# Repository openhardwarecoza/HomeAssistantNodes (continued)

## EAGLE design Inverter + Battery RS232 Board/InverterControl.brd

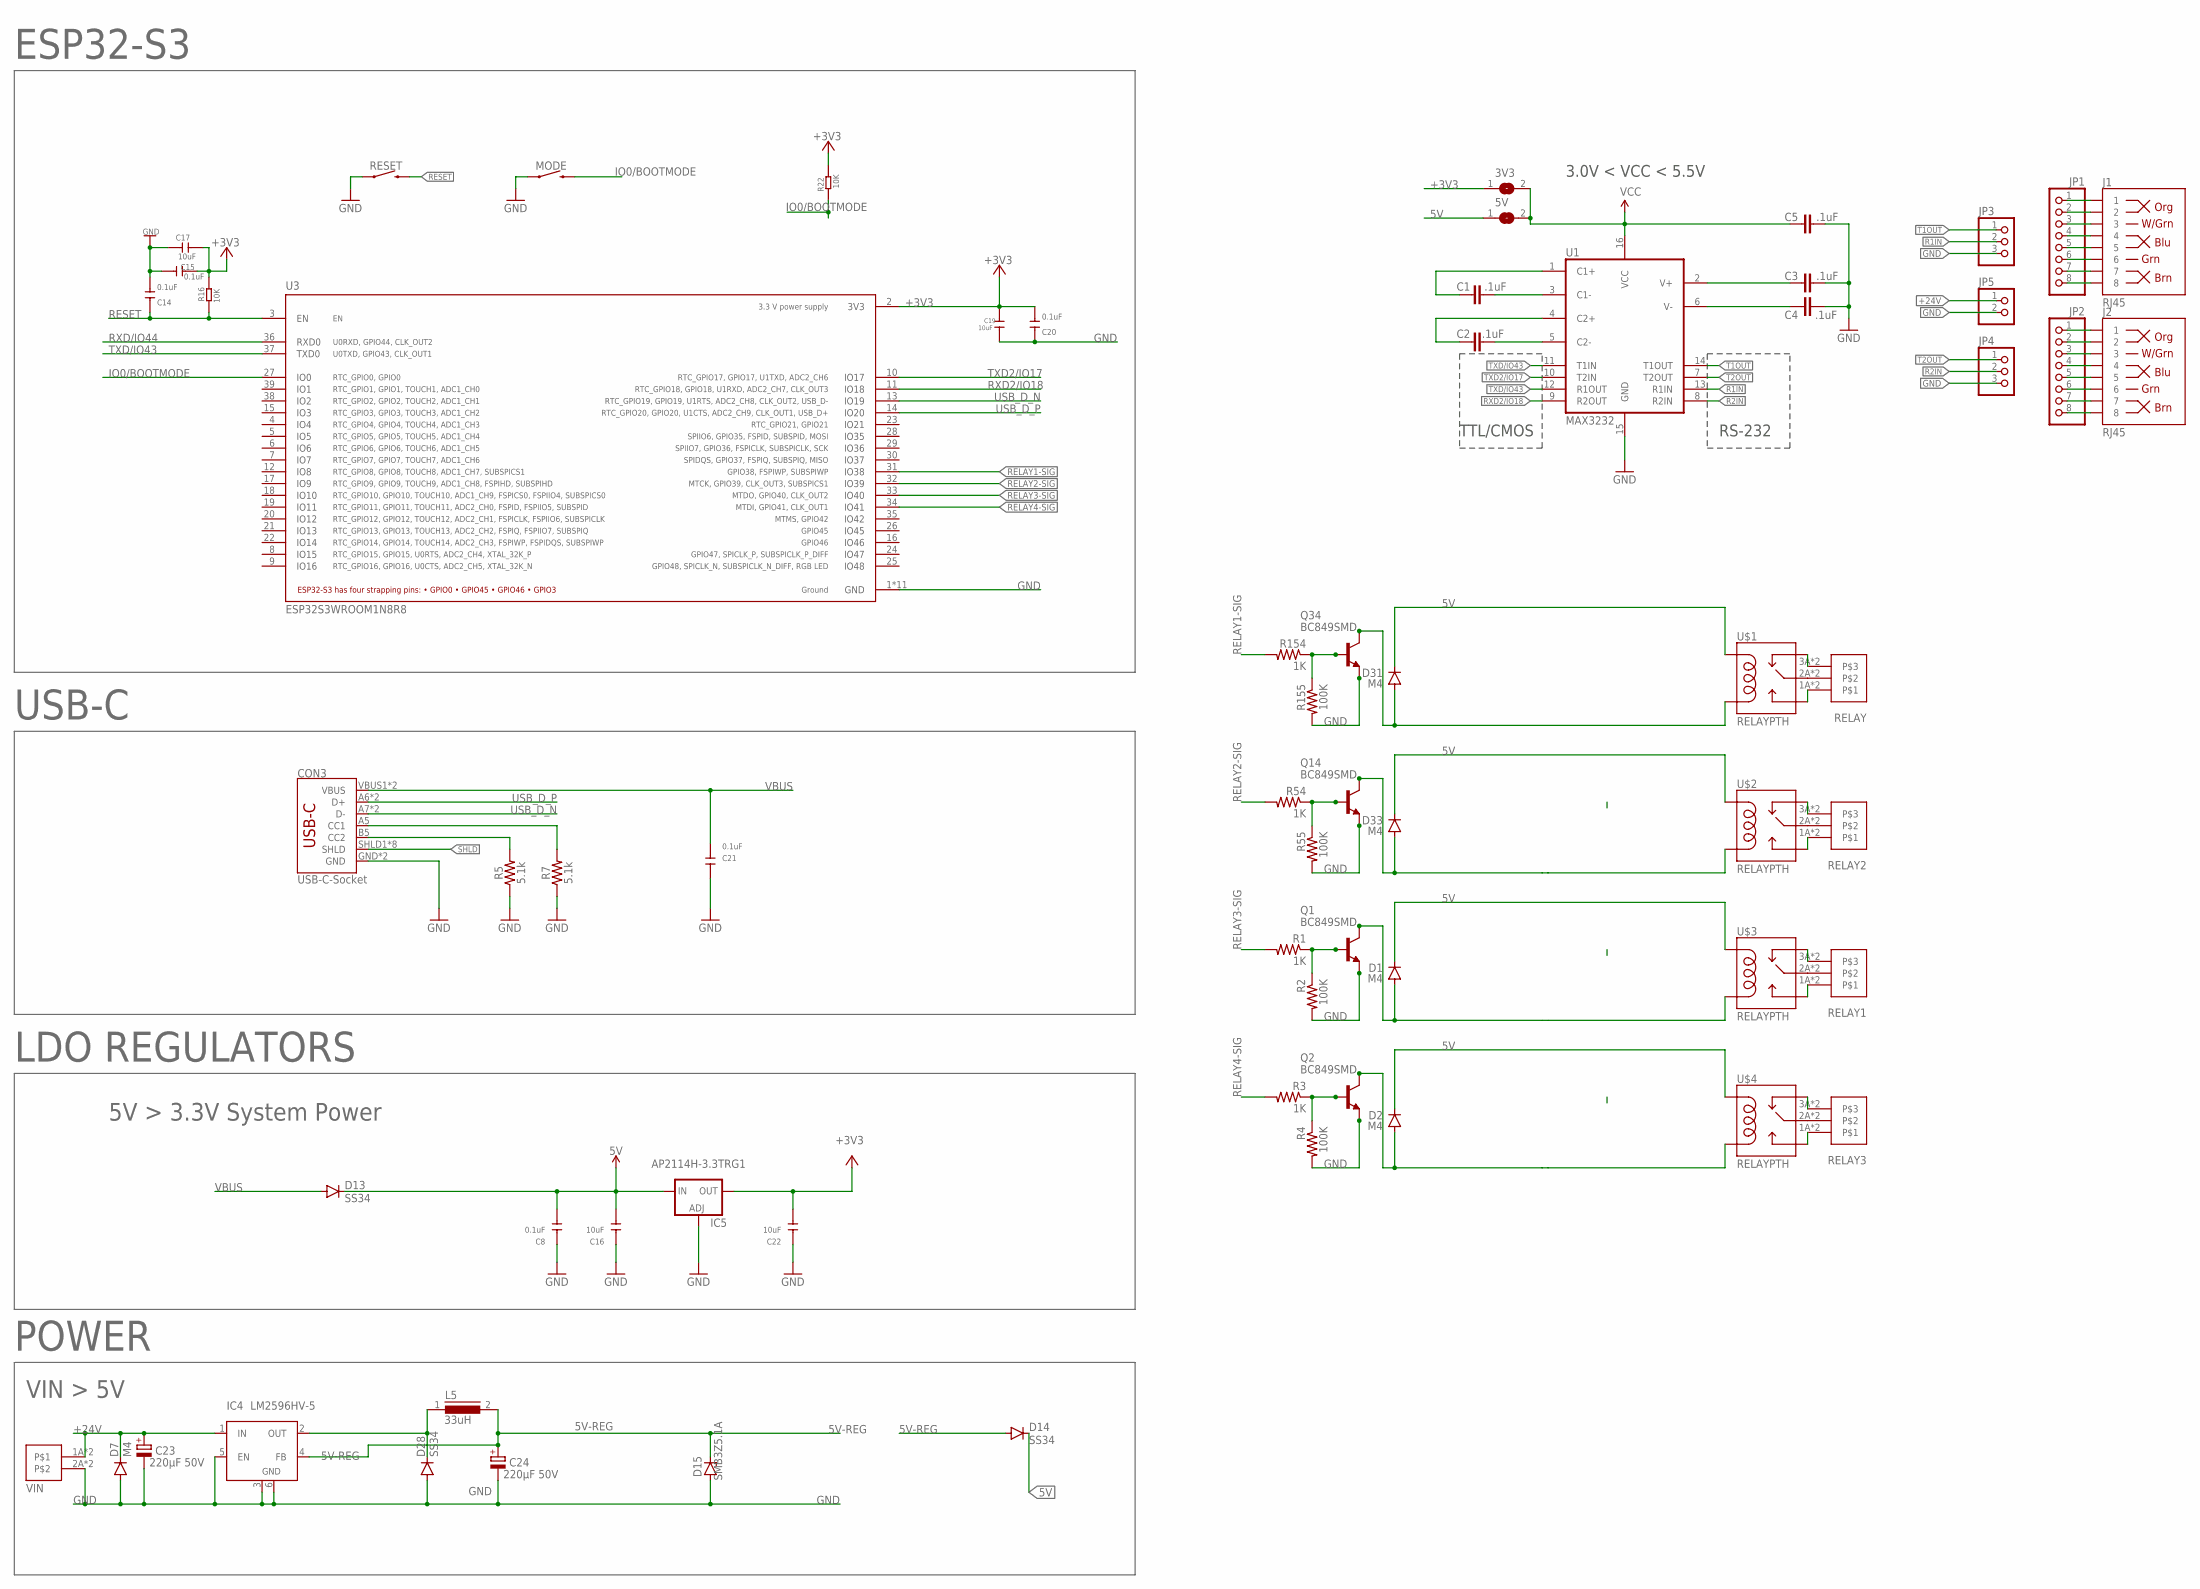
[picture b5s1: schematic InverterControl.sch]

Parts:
3V3, 5V: SJ
C1, C2, C3, C4, C5: .1uF; 0603-CAP
C8, C14, C15, C20, C21: 0.1uF; DISCRETE_C1206
C16, C19, C22: 10uF; C1206
C17: 10uF; DISCRETE_C1206
C23, C24: 220µF 50V; PANASONIC_E
CON3: USB-C-Socket; USB-C-16P
D1, D2, D7, D31, D33: M4; DO-214AC
D13: SS34; DO-214AC
D14, D28: SS34; SMB
D15: SMB3Z5.1A; SMB
IC4: LM2596HV-5; TO263-5
IC5: AP2114H-3.3TRG1; SOT223
J1, J2: RJ45; RJ45-8
JP1, JP2: PINHD-1X8; 1X08
JP3, JP4: PINHD-1X3; 1X03
JP5: PINHD-1X2; 1X02
L5: 33uH; DR127
MODE: MOMENTARY-SWITCH-SPST-PTH-6.0MM; TACTILE_SWITCH_PTH_6.0MM
Q1, Q2, Q14, Q34: BC849SMD; SOT23-BEC
R1, R3, R54, R154: 1K; R1206
R2, R4, R55, R155: 100K; R1206
R5, R7: 5.1k; 0603@1
R16, R22: 10K; R1206
RELAY, RELAY1, RELAY2, RELAY3: WJ212R-THR-3.5-3
RESET: MOMENTARY-SWITCH-SPST-PTH-6.0MM; TACTILE_SWITCH_PTH_6.0MM
U1: MAX3232; SO016
U3: ESP32S3WROOM1N8R8; XCVR_ESP32S3WROOM1N8R8
U$1, U$2, U$3, U$4: RELAYPTH; SRD-05VDC-SL-C
VIN: WJ212R-THR-3.5-2

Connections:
5V: 5V.1, C8.2, C16.1, D1.C, D2.C, D13.C, D14.C, D31.C, D33.C, IC5.3 (IN), U$1.COIL1, U$2.COIL1, U$3.COIL1, U$4.COIL1
5V-REG: C24.+, D14.A, D15.C, IC4.4 (FB), L5.2
+3V3: 3V3.1, C15.1, C17.1, C19.1, C20.2, C22.1, IC5.4 (OUT), R16.2, R22.2, U3.2 (3V3)
+24V: C23.+, D7.C, IC4.1 (IN), JP5.1, VIN.1A, VIN.1B
C1+: C1.1, U1.1 (C1+)
C1-: C1.2, U1.3 (C1-)
C2+: C2.1, U1.4 (C2+)
C2-: C2.2, U1.5 (C2-)
CC1: CON3.A5 (CC1), R7.2
CC2: CON3.B5 (CC2), R5.2
COIL-1: D31.A, Q34.C, U$1.COIL0
COIL-2: D33.A, Q14.C, U$2.COIL0
COIL-3: D1.A, Q1.C, U$3.COIL0
COIL-4: D2.A, Q2.C, U$4.COIL0
GND: C3.2, C4.2, C5.2, C8.1, C14.2, C15.2, C16.2, C17.2, C19.2, C20.1, C21.1, C22.2, C23.-, C24.-, CON3.GND, CON3.GND2 (GND), D7.A, D15.A, D28.A, IC4.3 (GND), IC4.5 (EN), IC4.6 (GND), IC5.1 (ADJ), JP3.3, JP4.3, JP5.2, MODE.1, Q1.E, Q2.E, Q14.E, Q34.E, R2.2, R4.2, R5.1, R7.1, R55.2, R155.2, RESET.1, U1.15 (GND), U3.1 (GND), U3.40 (GND), U3.41_1 (GND), U3.41_2 (GND), U3.41_3 (GND), U3.41_4 (GND), U3.41_5 (GND), U3.41_6 (GND), U3.41_7 (GND), U3.41_8 (GND), U3.41_9 (GND), VIN.2A, VIN.2B
IO0/BOOTMODE: MODE.3 (2), R22.1, U3.27 (IO0)
unnamed: J1.1, JP1.1
unnamed: J1.2, JP1.2
unnamed: J1.3, JP1.3
unnamed: J1.4, JP1.4
unnamed: J1.5, JP1.5
unnamed: J1.6, JP1.6
unnamed: J1.7, JP1.7
unnamed: J1.8, JP1.8
unnamed: J2.1, JP2.1
unnamed: J2.2, JP2.2
unnamed: J2.3, JP2.3
unnamed: J2.4, JP2.4
unnamed: J2.5, JP2.5
unnamed: J2.6, JP2.6
unnamed: J2.7, JP2.7
unnamed: J2.8, JP2.8
unnamed: RELAY.2A, RELAY.2B, U$1.SWCOMMON
unnamed: RELAY2.2A, RELAY2.2B, U$2.SWCOMMON
unnamed: Q1.B, R1.1, R2.1
unnamed: RELAY1.2A, RELAY1.2B, U$3.SWCOMMON
unnamed: Q2.B, R3.1, R4.1
unnamed: RELAY3.2A, RELAY3.2B, U$4.SWCOMMON
unnamed: RELAY.3A, RELAY.3B, U$1.SWCLOSED (SWCLOSE)
unnamed: RELAY.1A, RELAY.1B, U$1.SWOPEN
unnamed: RELAY2.3A, RELAY2.3B, U$2.SWCLOSED (SWCLOSE)
unnamed: RELAY2.1A, RELAY2.1B, U$2.SWOPEN
unnamed: RELAY1.3A, RELAY1.3B, U$3.SWCLOSED (SWCLOSE)
unnamed: RELAY1.1A, RELAY1.1B, U$3.SWOPEN
unnamed: Q14.B, R54.1, R55.1
unnamed: RELAY3.3A, RELAY3.3B, U$4.SWCLOSED (SWCLOSE)
unnamed: RELAY3.1A, RELAY3.1B, U$4.SWOPEN
unnamed: Q34.B, R154.1, R155.1
unnamed: D28.C, IC4.2 (OUT), L5.1
R1IN: JP3.2, U1.13 (R1IN)
R2IN: JP4.2, U1.8 (R2IN)
RELAY1-SIG: R154.2, U3.31 (IO38)
RELAY2-SIG: R54.2, U3.32 (IO39)
RELAY3-SIG: R1.2, U3.33 (IO40)
RELAY4-SIG: R3.2, U3.34 (IO41)
RESET: C14.1, R16.1, RESET.3 (2), U3.3 (EN)
RXD2/IO18: U1.9 (R2OUT), U3.11 (IO18)
RXD/IO44: U3.36 (RXD0)
SHLD: CON3.SHLD1 (SHLD), CON3.SHLD2 (SHLD), CON3.SHLD3 (SHLD), CON3.SHLD4 (SHLD), CON3.SHLD5 (SHLD), CON3.SHLD6 (SHLD), CON3.SHLD7 (SHLD), CON3.SHLD8 (SHLD)
T1OUT: JP3.1, U1.14 (T1OUT)
T2OUT: JP4.1, U1.7 (T2OUT)
TXD2/IO17: U1.10 (T2IN), U3.10 (IO17)
TXD/IO43: U1.11 (T1IN), U1.12 (R1OUT), U3.37 (TXD0)
USB_D_N: CON3.A7 (D-), CON3.B7 (D-), U3.13 (IO19)
USB_D_P: CON3.A6 (D+), CON3.B6 (D+), U3.14 (IO20)
V+: C3.1, U1.2 (V+)
V-: C4.1, U1.6 (V-)
VBUS: C21.2, CON3.VBUS1 (VBUS), CON3.VBUS2 (VBUS), D13.A
VCC: 3V3.2, 5V.2, C5.1, U1.16 (VCC)

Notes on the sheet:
ESP32-S3
5V > 3.3V System Power
USB-C
LDO REGULATORS
POWER
VIN > 5V
RS-232
TTL/CMOS
3.0V < VCC < 5.5V

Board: 4 copper layers, 67 parts (0 on the bottom side), 68 nets, no tracks yet.

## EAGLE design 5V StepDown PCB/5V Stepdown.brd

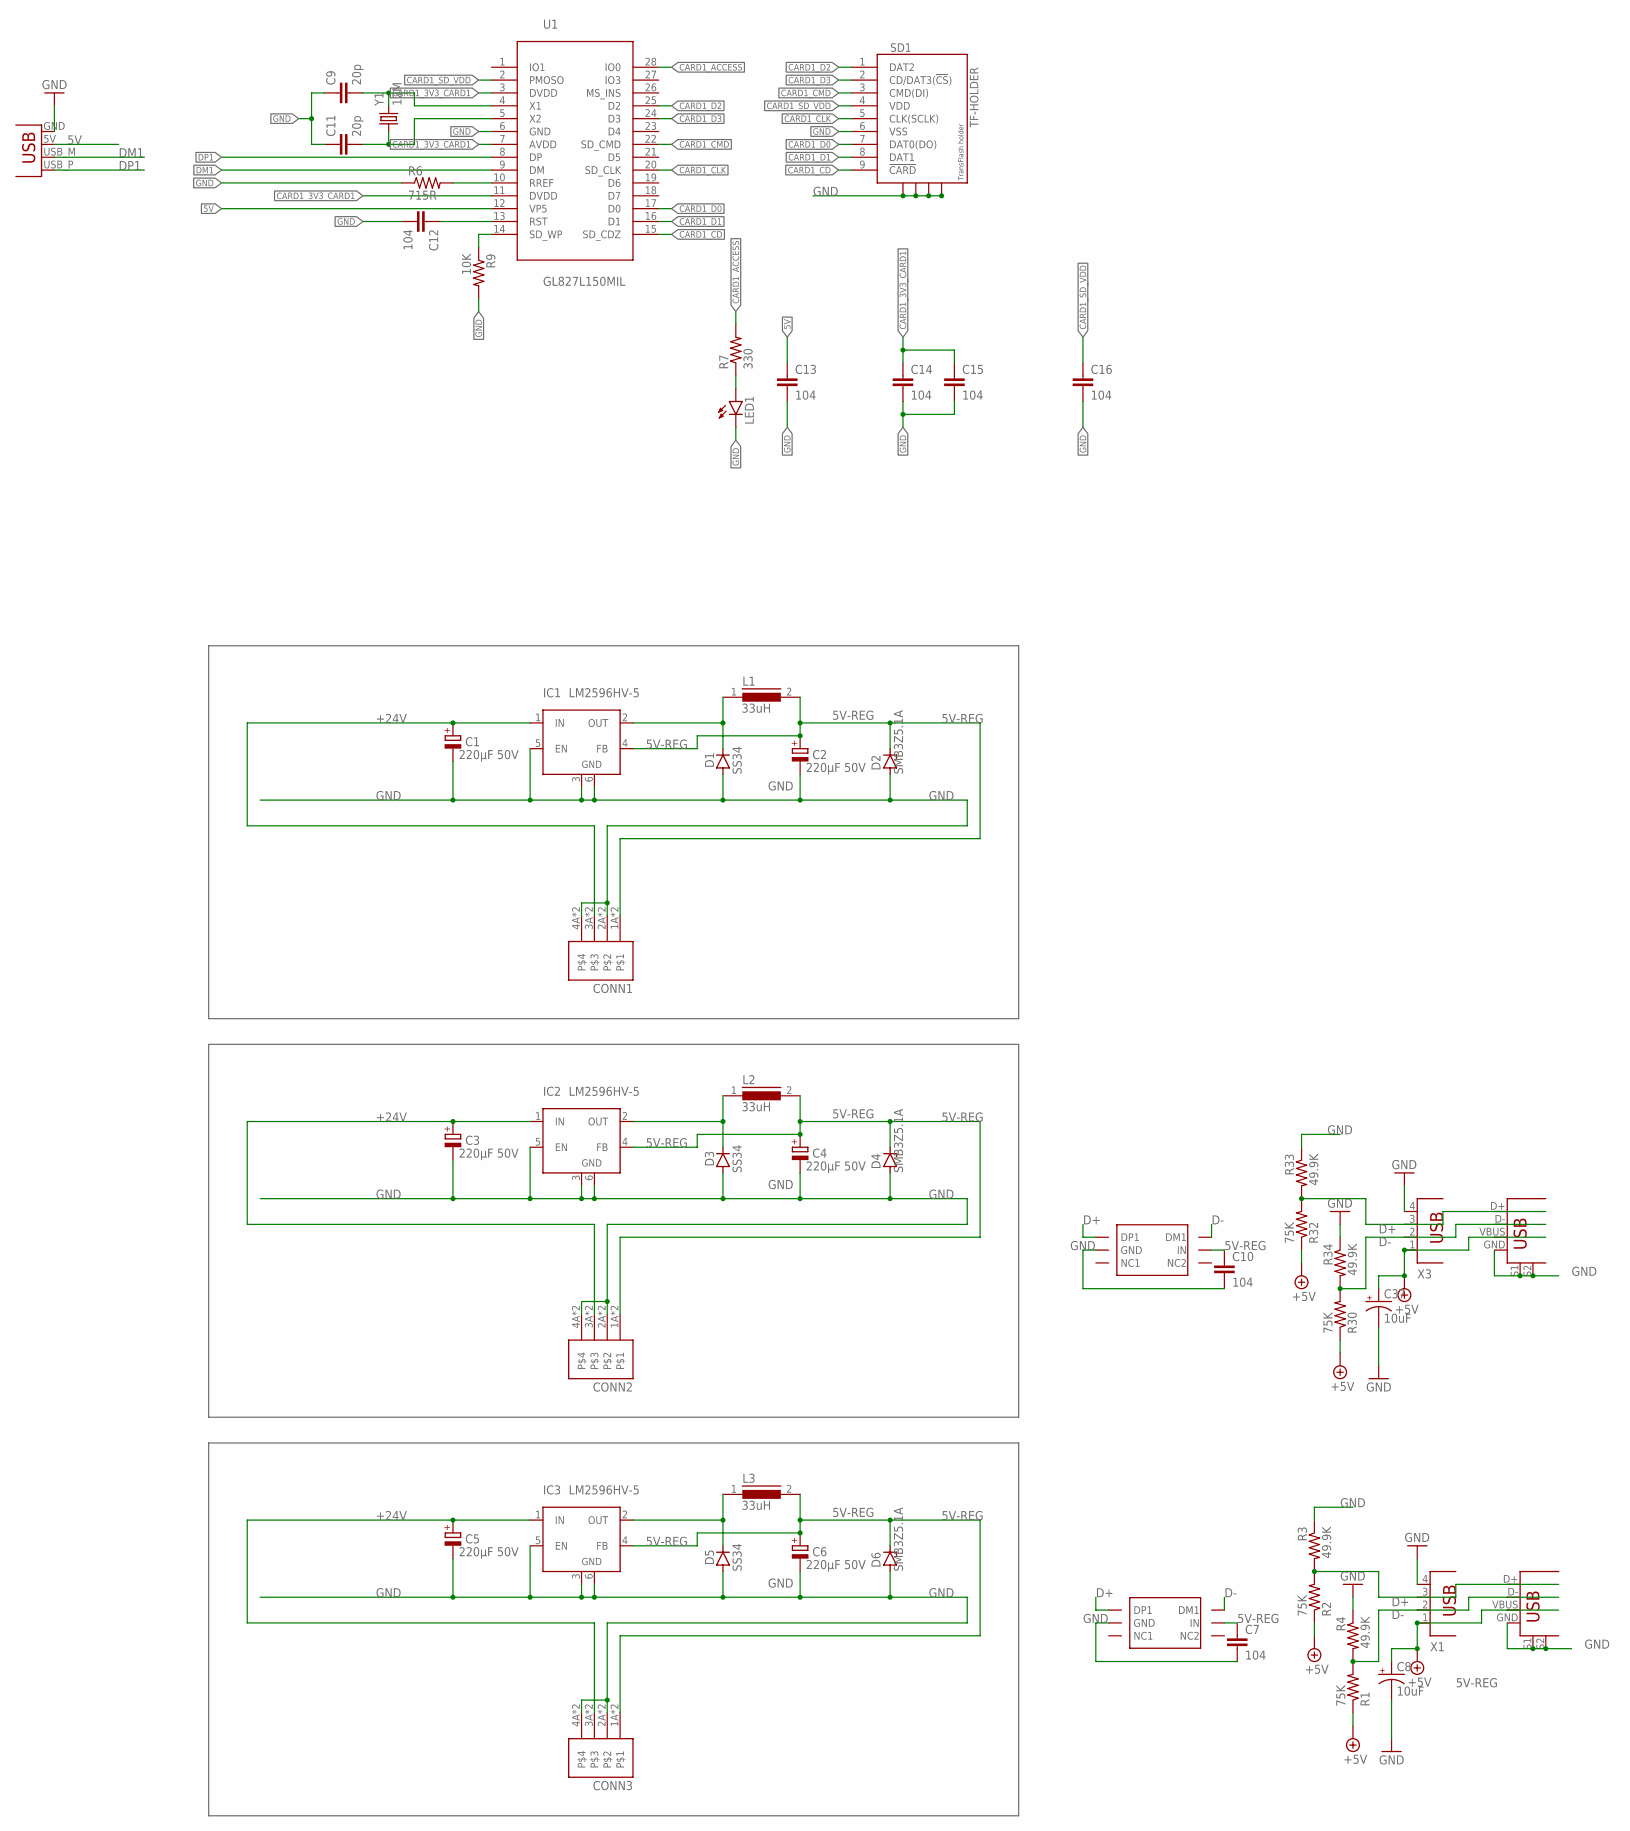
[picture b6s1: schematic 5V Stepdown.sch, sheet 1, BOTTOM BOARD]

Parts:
C1, C2, C3, C4, C5, C6: 220µF 50V; PANASONIC_E
C7, C10: 104; C1206
C8, C37: 10uF; EIA3216
C9, C11: 20p; 1206
C12, C13, C14, C15, C16: 104; 1206
CONN1, CONN2, CONN3: WJ212R-THR-3.5-4
D1, D3, D5: SS34; SOD87
D2, D4, D6: SMB3Z5.1A; SMB
IC1, IC2, IC3: LM2596HV-5; TO263-5
L1, L2, L3: 33uH; DR127
LED1: LED3MM
R1, R2, R30, R32: 75K; M1206
R3, R4, R33, R34: 49.9K; M1206
R6: 715R; 1206
R7: 330; 1206
R9: 10K; 1206
SD1: TF-HOLDER; TF-PULL
U1: GL827L150MIL; SSOP28-39
U$1, U$2: TPS2514
U$3, U$4: USB+SHIELDUSB-A-S-NOSILK-FEMALE; USB-A-S-NOSILK-FEMALE
X1, X3: PN87520
X2: USBPCB; USB-A-PCB
Y1: 12M; HC49US

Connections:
5V: C13.1, U1.12 (VP5), X2.5V (VBUS)
5V-REG: C2.+, C4.+, C6.+, C7.1, C8.A (+), C10.1, C37.A (+), CONN1.1A, CONN1.1B, CONN2.1A, CONN2.1B, CONN3.1A, CONN3.1B, D2.C, D4.C, D6.C, IC1.4 (FB), IC2.4 (FB), IC3.4 (FB), L1.2, L2.2, L3.2, R1.1, R2.1, R30.1, R32.1, U$1.IN, U$2.IN, U$3.VBUS, U$4.VBUS, X1.1, X3.1
+24V: C1.+, C3.+, C5.+, CONN1.3A, CONN1.3B, CONN2.3A, CONN2.3B, CONN3.3A, CONN3.3B, IC1.1 (IN), IC2.1 (IN), IC3.1 (IN)
CARD1_3V3_CARD1: C14.1, C15.1, U1.3 (DVDD), U1.7 (AVDD), U1.11 (DVDD)
CARD1_ACCESS: R7.2, U1.28 (IO0)
CARD1_CD: SD1.9 (!CARD), U1.15 (SD_CDZ)
CARD1_CLK: SD1.5 (CLK(SCLK)), U1.20 (SD_CLK)
CARD1_CMD: SD1.3 (CMD(DI)), U1.22 (SD_CMD)
CARD1_D0: SD1.7 (DAT0(DO)), U1.17 (D0)
CARD1_D1: SD1.8 (DAT1), U1.16 (D1)
CARD1_D2: SD1.1 (DAT2), U1.25 (D2)
CARD1_D3: SD1.2 (CD/DAT3(!CS!)), U1.24 (D3)
CARD1_SD_VDD: C16.1, SD1.4 (VDD), U1.2 (PMOSO)
D+: R2.2, R3.2, R32.2, R33.2, U$1.DP1, U$2.DP1, U$3.D+, U$4.D+, X1.3, X3.3
D-: R1.2, R4.2, R30.2, R34.2, U$1.DM1, U$2.DM1, U$3.D-, U$4.D-, X1.2, X3.2
DM1: U1.9 (DM), X2.USB_M (D-)
DP1: U1.8 (DP), X2.USB_P (D+)
GND: C1.-, C2.-, C3.-, C4.-, C5.-, C6.-, C7.2, C8.C (-), C9.1, C10.2, C11.1, C12.2, C13.2, C14.2, C15.2, C16.2, C37.C (-), CONN1.2A, CONN1.2B, CONN1.4A, CONN1.4B, CONN2.2A, CONN2.2B, CONN2.4A, CONN2.4B, CONN3.2A, CONN3.2B, CONN3.4A, CONN3.4B, D1.2 (A), D2.A, D3.2 (A), D4.A, D5.2 (A), D6.A, IC1.3 (GND), IC1.5 (EN), IC1.6 (GND), IC2.3 (GND), IC2.5 (EN), IC2.6 (GND), IC3.3 (GND), IC3.5 (EN), IC3.6 (GND), LED1.K (C), R3.1, R4.1, R6.1, R9.2, R33.1, R34.1, SD1.6 (VSS), SD1.S1, SD1.S2, SD1.S3, SD1.S4, U1.6 (GND), U$1.GND, U$2.GND, U$3.GND, U$3.S1, U$3.S2, U$4.GND, U$4.S1, U$4.S2, X1.4, X2.GND, X3.4
unnamed: C9.2, U1.4 (X1), Y1.2
unnamed: C11.2, U1.5 (X2), Y1.1
unnamed: R6.2, U1.10 (RREF)
unnamed: C12.1, U1.13 (RST)
unnamed: LED1.A, R7.1
unnamed: R9.1, U1.14 (SD_WP)
SW-L: D1.1 (C), IC1.2 (OUT), L1.1
SW-L1: D3.1 (C), IC2.2 (OUT), L2.1
SW-L2: D5.1 (C), IC3.2 (OUT), L3.1

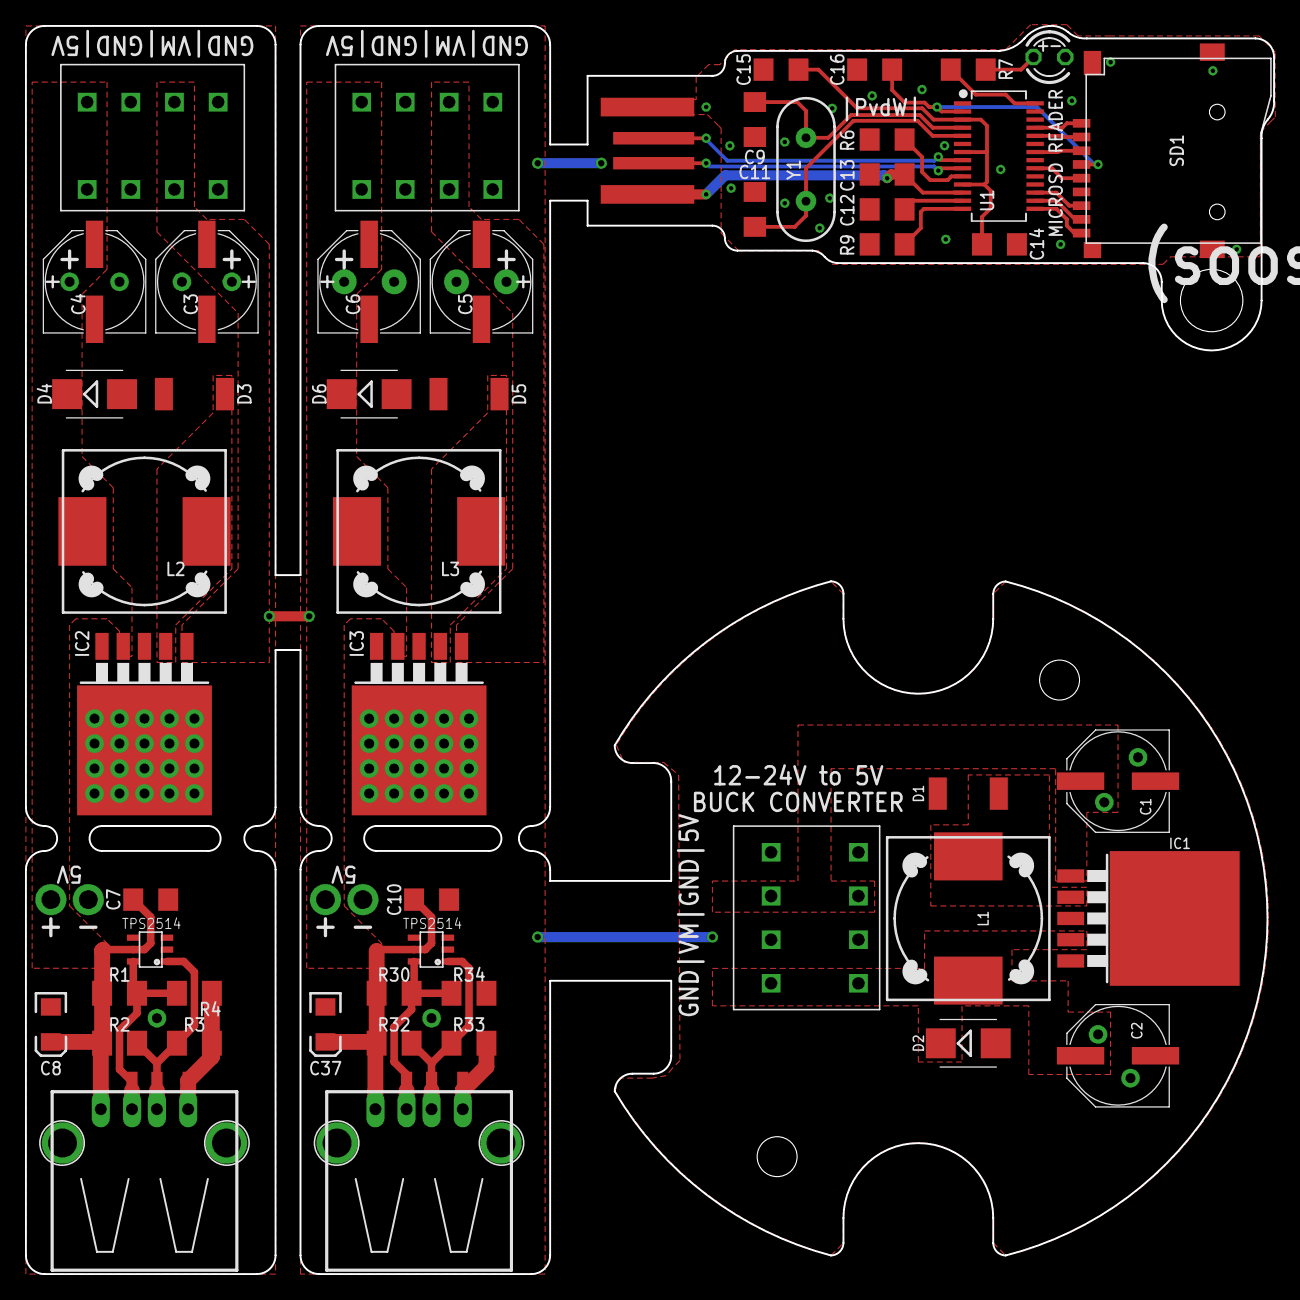
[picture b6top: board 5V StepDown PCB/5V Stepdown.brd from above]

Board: 2 copper layers, 100.0 x 100.0 mm, 54 parts (0 on the bottom side), 27 nets.

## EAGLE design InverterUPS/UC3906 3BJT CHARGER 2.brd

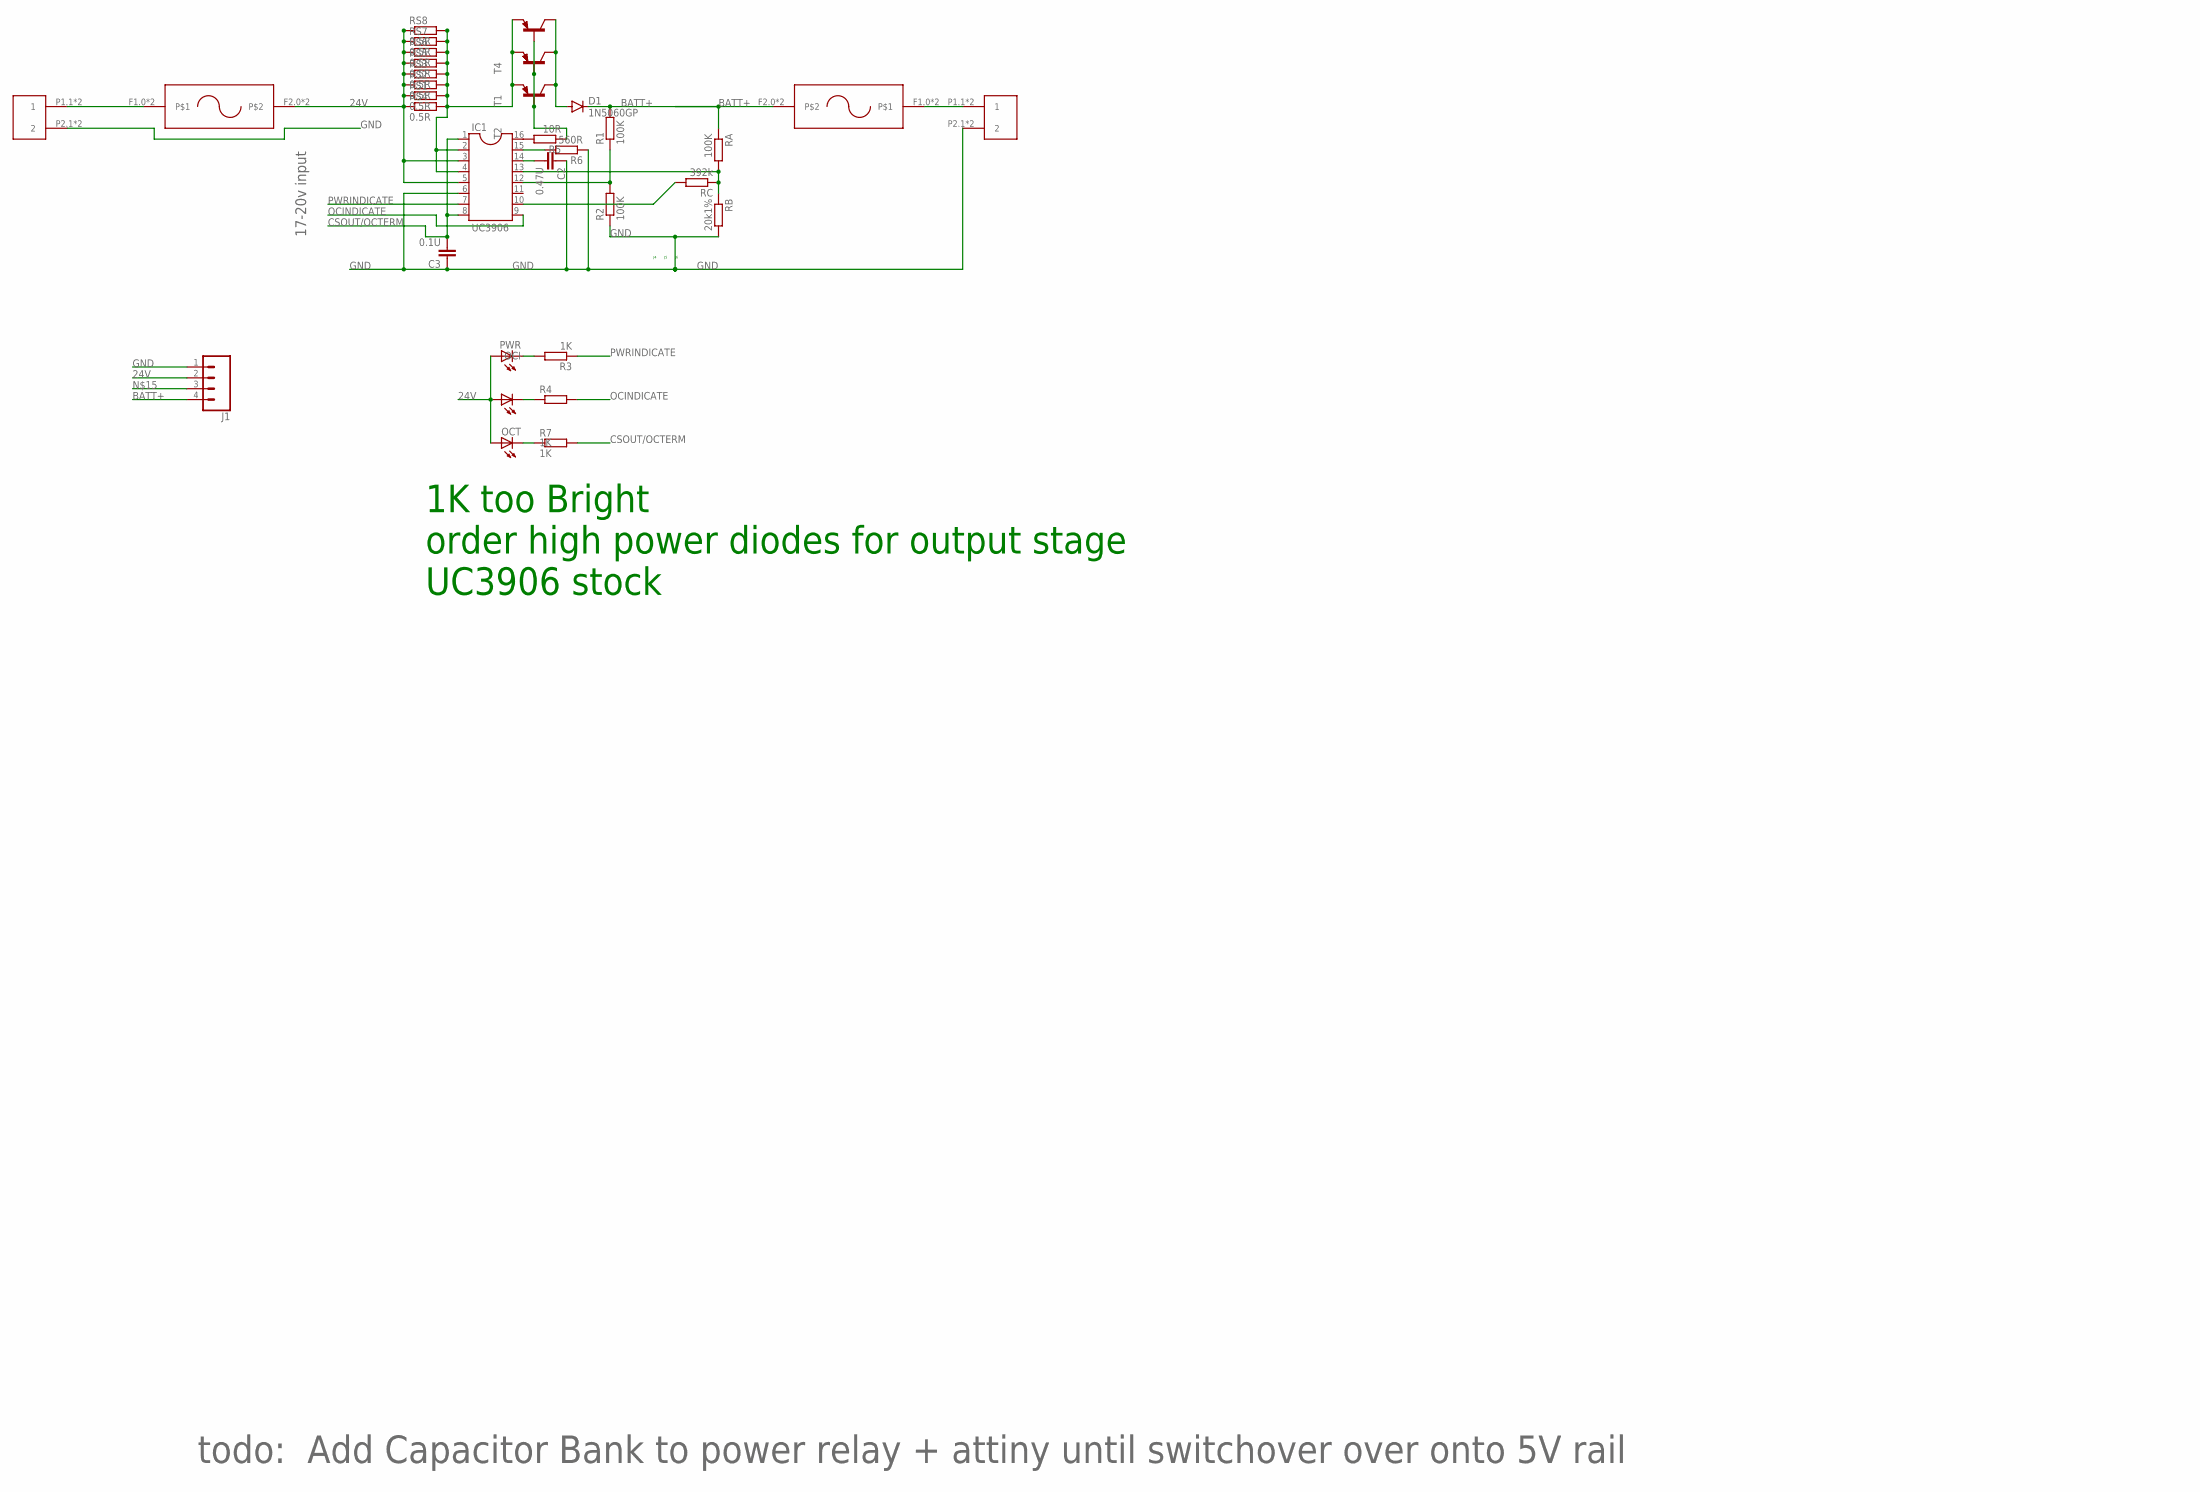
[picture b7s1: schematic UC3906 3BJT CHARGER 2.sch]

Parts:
BATT: BARRIERTERMINAL
C2: 0.47U; C050-024X044
C3: 0.1U; C050-024X044
D1: 1N5060GP; DO15-12
IC1: UC3906; DIL16
J1: CONN_04LONGPADS; 1X04_LONGPADS
OCI: LED5MM
OCT: LED5MM
POWERIN: BARRIERTERMINAL
PWR: LED5MM
R1, R2: 100K; 0204/7
R3, R4, R7: 1K; 0204/7
R5: 10R; 0204/7
R6: 560R; 0204/7
RA: 100K; 0204/7
RB: 20k1%; 0204/7
RC: 392k; 0204/7
RS1, RS2, RS3, RS4, RS5, RS6, RS7, RS8: 0.5R; 0411/15
T1, T2, T4: -PNP-TO220V; TO220V
U$1, U$2: 18MMFUSEHOLDER

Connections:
24V: IC1.3, IC1.5, J1.2, OCI.A, OCT.A, PWR.A, RS1.1, RS2.1, RS3.1, RS4.1, RS5.1, RS6.1, RS7.1, RS8.1, U$2.F2.0, U$2.F2.1
BATT+: D1.C, J1.4, R1.2, RA.1, U$1.F2.0, U$1.F2.1
CHARGEENABLE: IC1.12, R1.1, R2.2
COMPENSATION: C2.2, IC1.14
CSOUT/OCTERM: C3.2, IC1.1, IC1.8, R7.2
DRIVERSINK: IC1.16, R5.2
DRIVERSOURCE: IC1.15, R6.2
GND: BATT.P2.1 (2), BATT.P2.2 (2), C2.1, C3.1, IC1.6, J1.1, POWERIN.P2.1 (2), POWERIN.P2.2 (2), R2.1, R6.1, RB.2
IOUT: IC1.2, IC1.4, RS1.2, RS2.2, RS3.2, RS4.2, RS5.2, RS6.2, RS7.2, RS8.2, T1.3 (E), T2.3 (E), T4.3 (E)
unnamed: POWERIN.P1.1 (1), POWERIN.P1.2 (1), U$2.F1.0, U$2.F1.1
unnamed: PWR.K (C), R3.2
unnamed: OCI.K (C), R4.1
unnamed: OCT.K (C), R7.1
unnamed: BATT.P1.1 (1), BATT.P1.2 (1), U$1.F1.0, U$1.F1.1
unnamed: R5.1, T1.1 (B), T2.1 (B), T4.1 (B)
unnamed: D1.A, J1.3, T1.2 (C), T2.2 (C), T4.2 (C)
OCINDICATE: IC1.9, R4.2
PWRINDICATE: IC1.7, R3.1
STATELEVELCONTROL: IC1.10, RC.2
VSENSE: IC1.13, RA.2, RB.1, RC.1

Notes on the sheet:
17-20v input
todo: Add Capacitor Bank to power relay + attiny until switchover over onto 5V rail
1K too Bright order high power diodes for output stage UC3906 stock

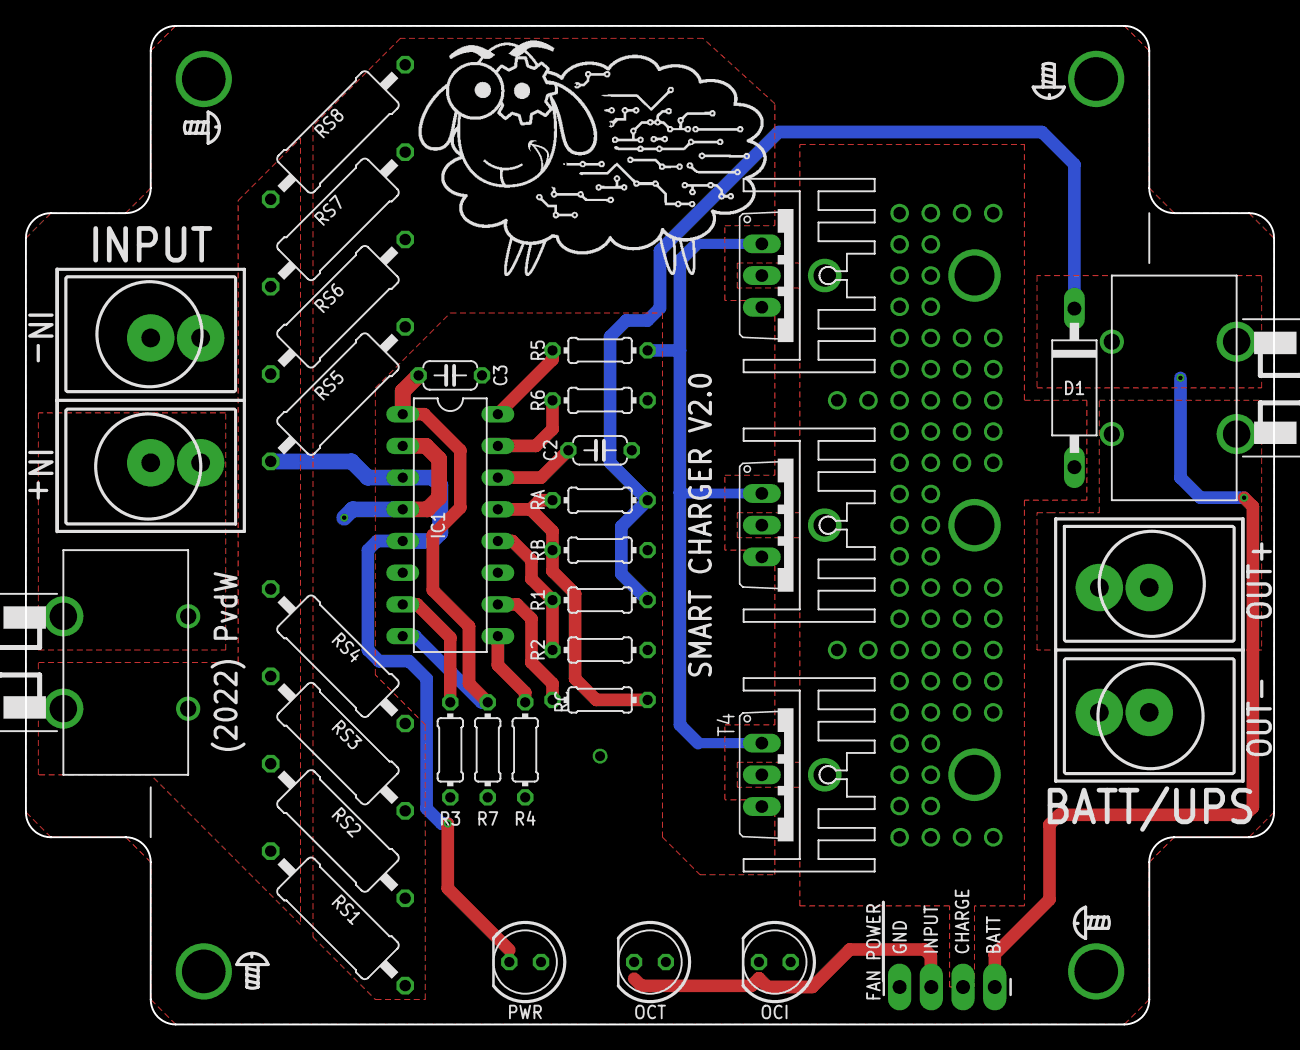
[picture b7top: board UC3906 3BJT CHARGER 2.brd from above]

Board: 2 copper layers, 100.0 x 80.0 mm, 33 parts (0 on the bottom side), 20 nets.

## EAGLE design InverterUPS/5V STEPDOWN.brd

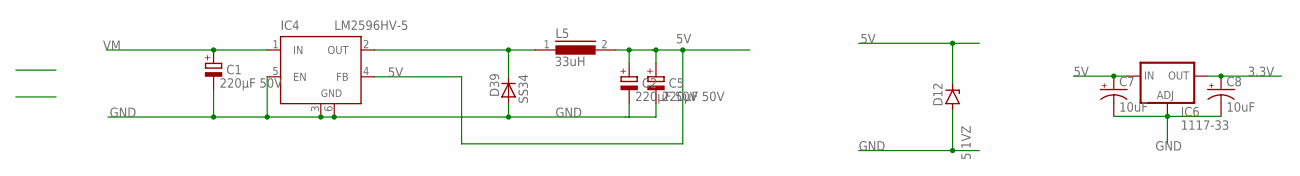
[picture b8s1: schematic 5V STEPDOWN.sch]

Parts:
C1, C2, C5: 220µF 50V; E3,5-8
C7, C8: 10uF; CPOL-RADIAL-10UF-25V
D12: 5.1VZ; SMB
D39: SS34; SOD87
IC4: LM2596HV-5; TO263-5
IC6: 1117-33; SOT223
L5: 33uH; DR127

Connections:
3.3V: C8.1 (+), IC6.4 (OUT)
5V: C2.+, C5.+, C7.1 (+), D12.C, IC4.4 (FB), IC6.3 (IN), L5.2
GND: C1.-, C2.-, C5.-, C7.2 (-), C8.2 (-), D12.A, D39.2 (A), IC4.3 (GND), IC4.5 (EN), IC4.6 (GND), IC6.1 (ADJ)
unnamed: D39.1 (C), IC4.2 (OUT), L5.1
VM: C1.+, IC4.1 (IN)

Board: 2 copper layers, 10 parts (0 on the bottom side), 5 nets, no tracks yet.

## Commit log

2021-11-30 save
2023-08-21 DB board
2024-01-10 PCB5102 Board
2024-01-23 PCN5102 board
2024-12-29 sycned local
